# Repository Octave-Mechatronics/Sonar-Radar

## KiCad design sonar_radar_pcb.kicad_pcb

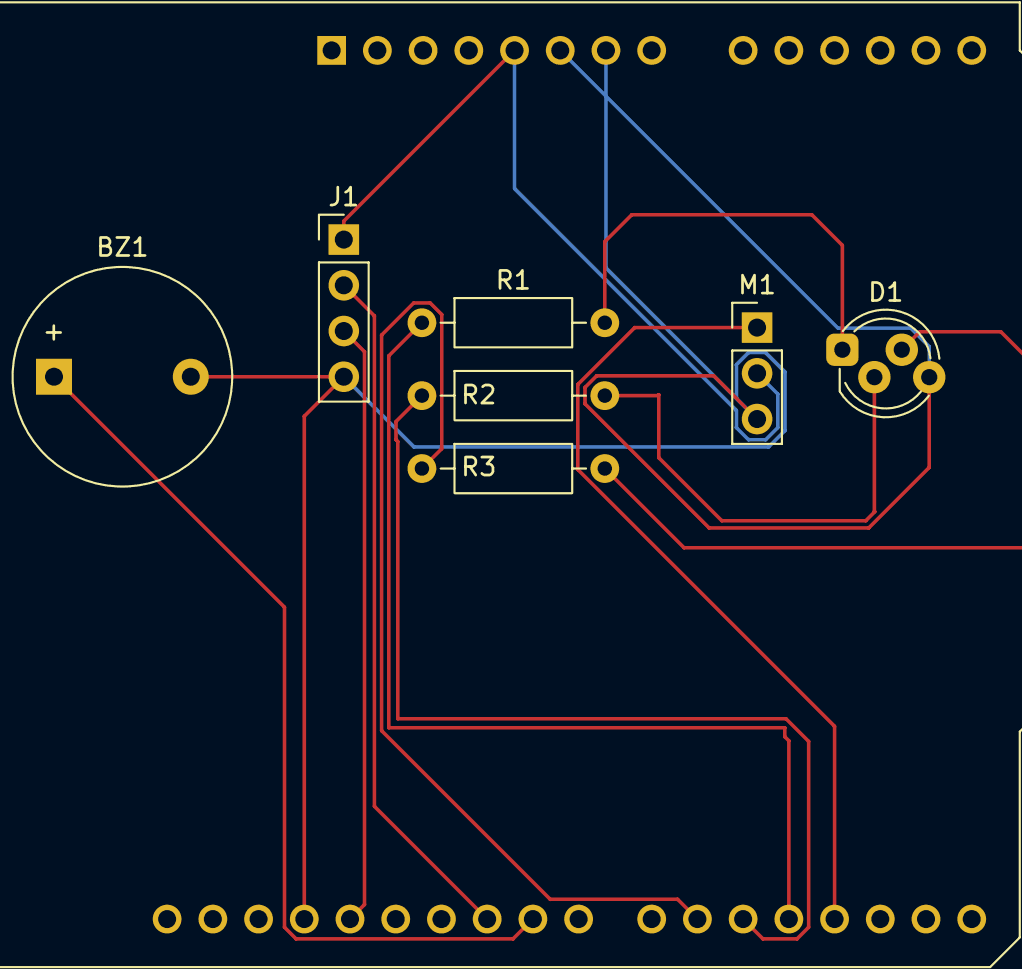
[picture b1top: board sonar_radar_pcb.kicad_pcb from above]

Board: 2 copper layers, 8 parts (0 on the bottom side), 12 nets.

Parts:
A1: Arduino_UNO_R3
BZ1: Buzzer; Buzzer_12x9.5RM7.6
D1: LED_RGB; LED_D5.0mm-4_RGB_Staggered_Pins
J1: Conn_01x04; PinHeader_1x04_P2.54mm_Vertical
M1: Motor_Servo; PinHeader_1x03_P2.54mm_Vertical
R1, R2, R3: 220; R_Axial_DIN0207_L6.3mm_D2.5mm_P10.16mm_Horizontal

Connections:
GND: A1.6 (GND), A1.7 (GND), A1.29 (GND), BZ1.2 (-), D1.4 (BA), J1.4, M1.3 (-)
unnamed: A1.5 (+5V), J1.1, M1.2 (+)
unnamed: A1.18 (D3), M1.1 (PWM)
unnamed: A1.19 (D4), R1.1
unnamed: A1.20 (D5), R2.1
unnamed: A1.21 (D6), R3.1
unnamed: A1.24 (D9), BZ1.1 (+)
unnamed: A1.25 (D10), J1.2
unnamed: A1.28 (D13), J1.3
unnamed: D1.3 (BK), R3.2
unnamed: D1.2 (GK), R2.2
unnamed: D1.1 (RK), R1.2
